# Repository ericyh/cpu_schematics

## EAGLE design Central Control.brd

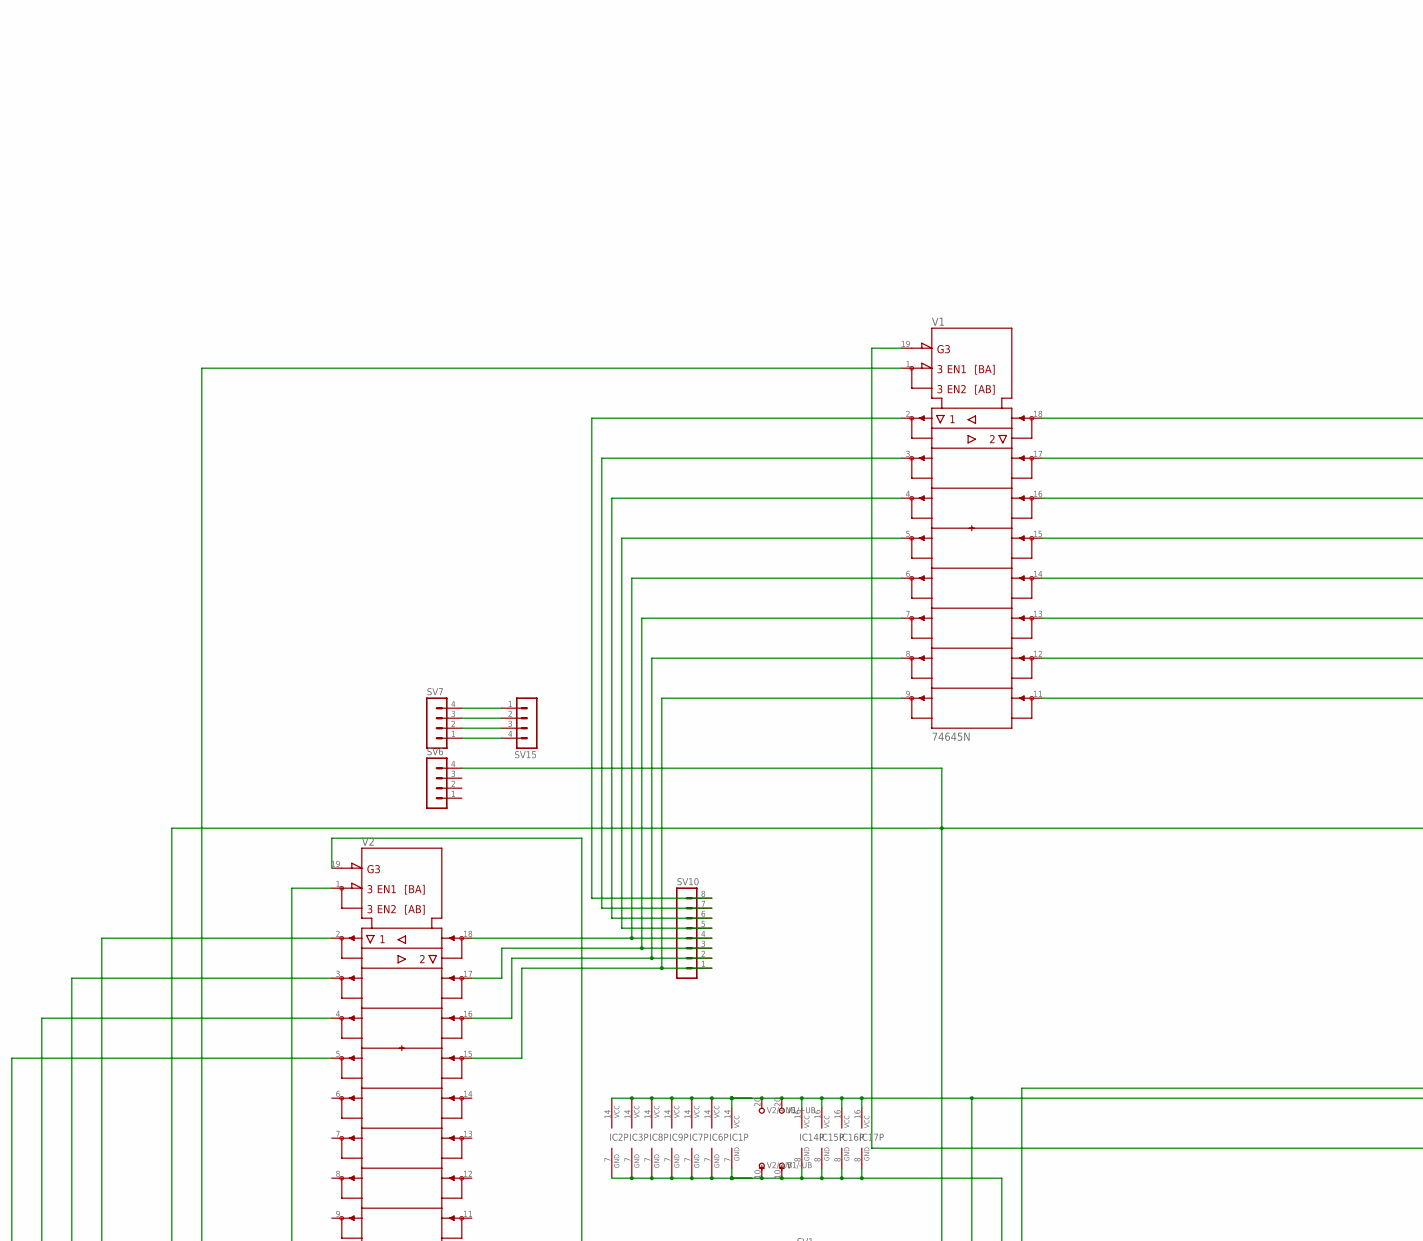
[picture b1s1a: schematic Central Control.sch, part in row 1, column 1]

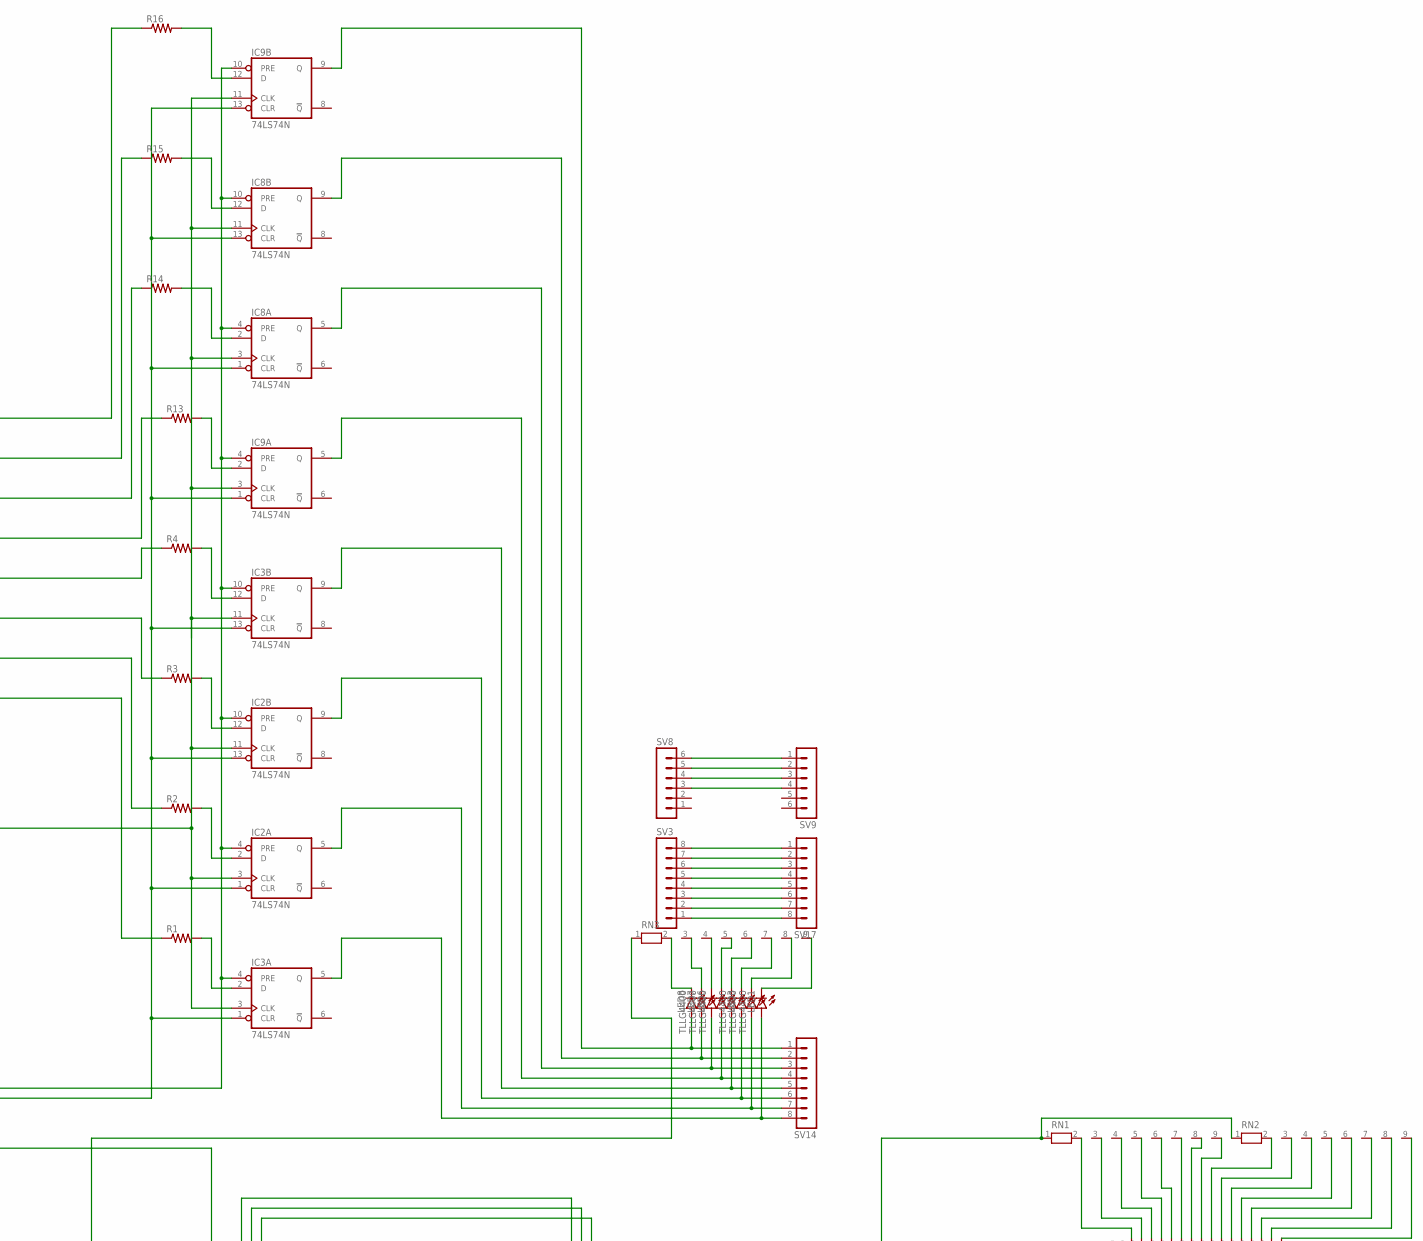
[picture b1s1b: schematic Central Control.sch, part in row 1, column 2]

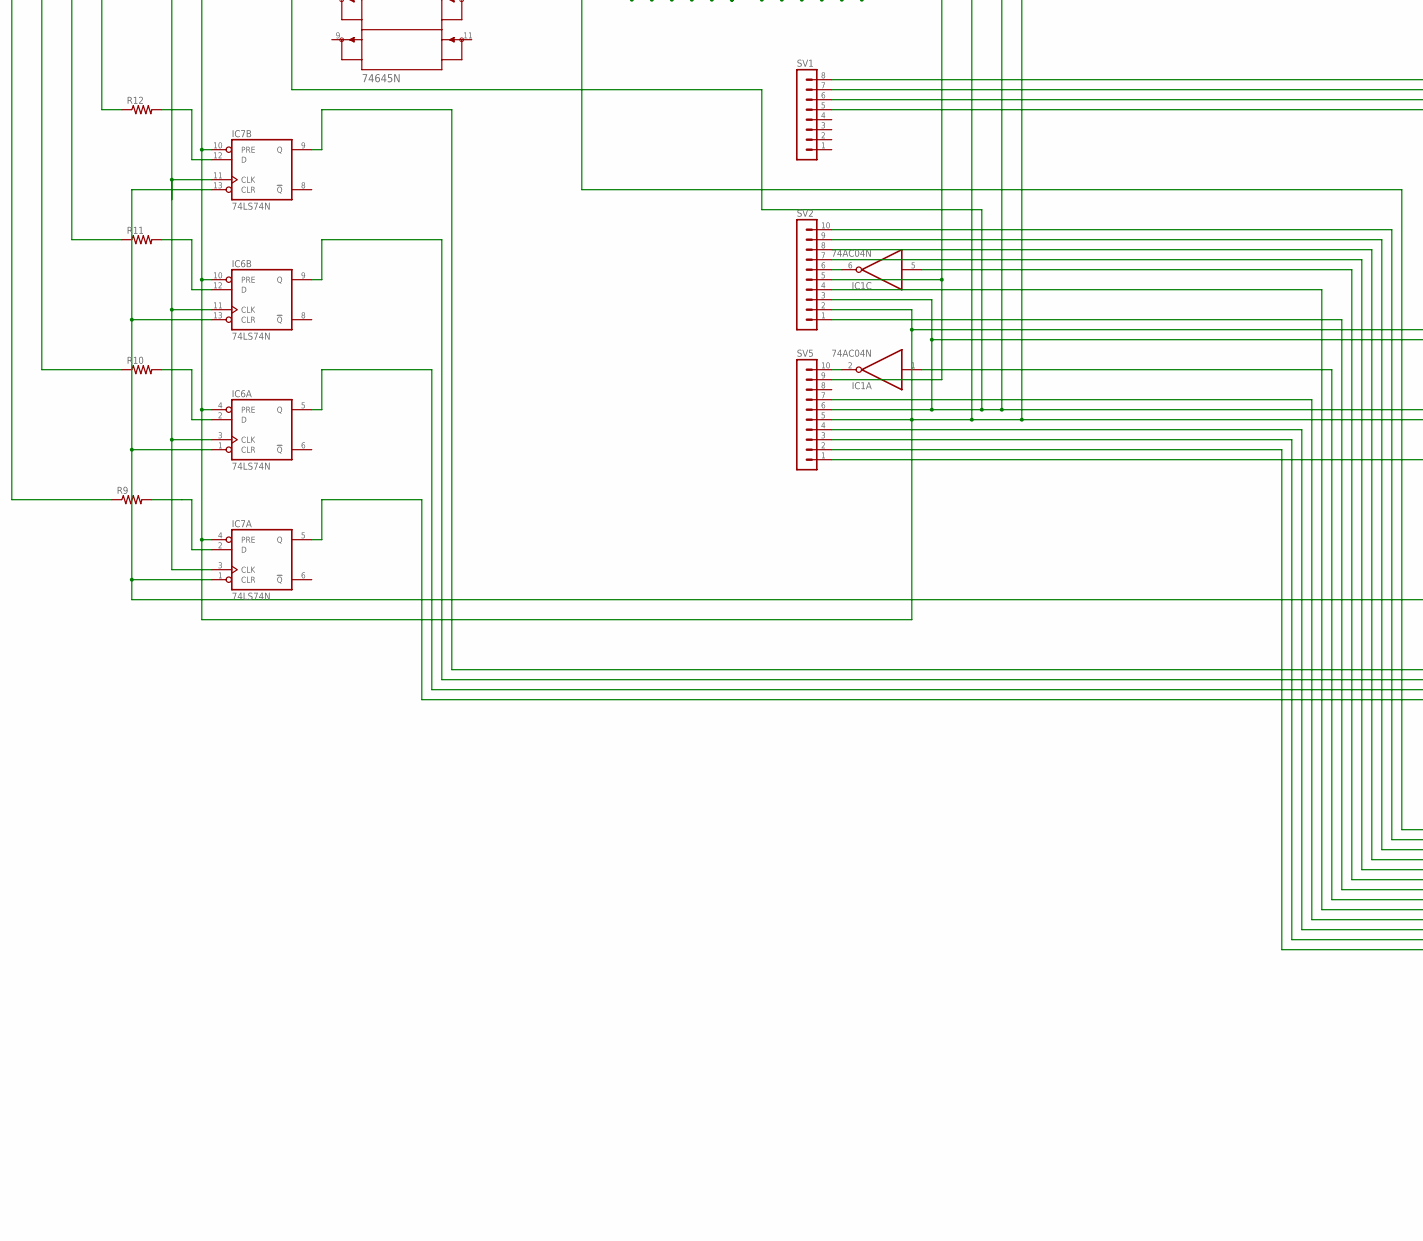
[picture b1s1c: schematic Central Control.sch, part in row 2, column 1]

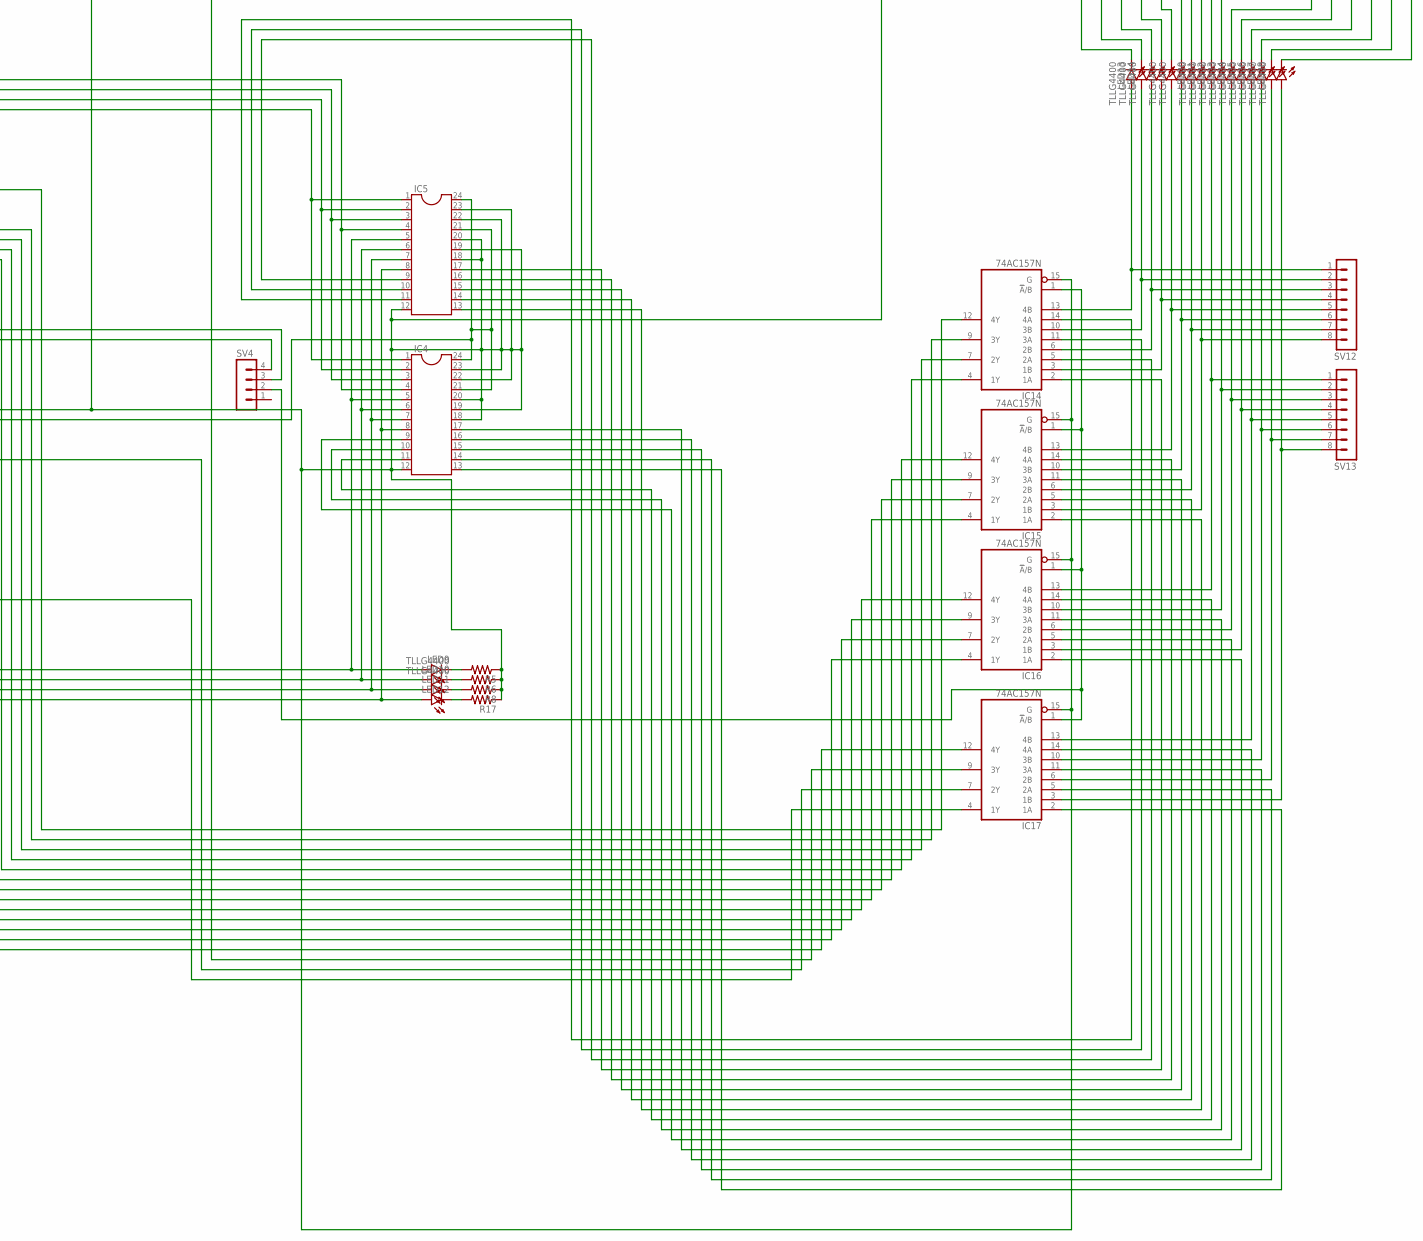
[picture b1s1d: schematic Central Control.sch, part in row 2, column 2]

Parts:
IC1: 74AC04N; DIL14
IC2, IC3, IC6, IC7, IC8, IC9: 74LS74N; DIL14
IC4, IC5: DIL24-6
IC14, IC15, IC16, IC17: 74AC157N; DIL16
LED1, LED2, LED3, LED4, LED5, LED6, LED7, LED8, LED9, LED10, LED11, LED12, LED13, LED14, LED15, LED16, LED18, LED19, LED20, LED21, LED22, LED23, LED24, LED25, LED26, LED27, LED28, LED29: TLLG4400; LED3MM
R1, R2, R3, R4, R5, R6, R8, R9, R10, R11, R12, R13, R14, R15, R16, R17: R-US_0207/2V; 0207/2V
RN1, RN2, RN3: RN08; RN-9
SV1, SV3, SV10, SV12, SV13, SV14, SV17: MA08-1
SV2, SV5: MA10-1
SV4, SV6, SV7, SV15: MA04-1
SV8, SV9: MA06-1
V1, V2: 74645N; DIL20

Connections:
unnamed: IC1.5 (I), IC15.9 (3Y)
unnamed: IC4.8, IC5.8, IC7.5 (Q), LED12.A
unnamed: IC14.13 (4B), LED13.A, SV12.1
unnamed: IC4.14, IC17.5 (2A)
unnamed: IC17.3 (1B), LED29.A, SV13.8
unnamed: SV10.5, V1.5 (A4)
unnamed: SV10.6, V1.4 (A3)
unnamed: SV10.7, V1.3 (A2)
unnamed: SV10.8, V1.2 (A1)
unnamed: SV10.4, V1.6 (A5), V2.18 (B1)
unnamed: IC4.1, IC5.1, SV1.5
unnamed: SV10.3, V1.7 (A6), V2.17 (B2)
unnamed: R10.1, V2.4 (A3)
unnamed: R9.1, V2.5 (A4)
unnamed: IC1.1 (I), IC15.4 (1Y)
unnamed: IC3.9 (Q), LED4.A, SV14.5
unnamed: IC17.6 (2B), LED28.A, SV13.7
unnamed: IC17.10 (3B), LED27.A, SV13.6
unnamed: IC4.16, IC17.14 (4A)
unnamed: IC1.7 (GND), IC2.7 (GND), IC3.7 (GND), IC4.12, IC4.18, IC4.19, IC4.20, IC4.22, IC4.23, IC5.12, IC5.18, IC5.19, IC5.20, IC5.22, IC5.23, IC6.7 (GND), IC7.7 (GND), IC8.7 (GND), IC9.7 (GND), IC14.8 (GND), IC14.15 (G), IC15.8 (GND), IC15.15 (G), IC16.8 (GND), IC16.15 (G), IC17.8 (GND), IC17.15 (G), R5.1, R6.1, R8.1, R17.1, RN1.1, RN2.1, RN3.1, SV2.3, SV4.4, SV5.6, V1.10 (-UB), V2.1 (DIR), V2.10 (-UB)
unnamed: IC5.10, IC14.11 (3A)
unnamed: IC5.11, IC14.14 (4A)
unnamed: IC16.13 (4B), LED22.A, SV13.1
unnamed: IC16.10 (3B), LED23.A, SV13.2
unnamed: IC16.6 (2B), LED24.A, SV13.3
unnamed: IC16.3 (1B), LED25.A, SV13.4
unnamed: IC17.13 (4B), LED26.A, SV13.5
unnamed: IC4.13, IC17.2 (1A)
unnamed: IC2.3 (CLK), IC2.11 (CLK), IC3.3 (CLK), IC3.11 (CLK), IC6.3 (CLK), IC6.11 (CLK), IC7.3 (CLK), IC7.11 (CLK), IC8.3 (CLK), IC8.11 (CLK), IC9.3 (CLK), IC9.11 (CLK), SV2.5, SV5.9, SV6.4
unnamed: IC4.5, IC5.5, IC7.9 (Q), LED9.A
unnamed: R3.1, V1.13 (B6)
unnamed: R4.1, V1.14 (B5)
unnamed: IC4.6, IC5.6, IC6.9 (Q), LED10.A
unnamed: IC4.7, IC5.7, IC6.5 (Q), LED11.A
unnamed: R1.1, V1.11 (B8)
unnamed: IC2.9 (Q), LED3.A, SV14.6
unnamed: IC2.5 (Q), LED2.A, SV14.7
unnamed: IC3.5 (Q), LED1.A, SV14.8
unnamed: IC4.2, IC5.2, SV1.6
unnamed: IC4.4, IC5.4, SV1.8
unnamed: R14.1, V1.16 (B3)
unnamed: IC4.3, IC5.3, SV1.7
unnamed: IC17.9 (3Y), V1.19 (!G)
unnamed: IC6.1 (CLR), IC6.13 (CLR), IC7.1 (CLR), IC7.13 (CLR), IC17.4 (1Y)
unnamed: SV7.4, SV15.1
unnamed: R13.1, V1.15 (B4)
unnamed: IC9.9 (Q), LED8.A, SV14.1
unnamed: IC8.9 (Q), LED7.A, SV14.2
unnamed: IC9.5 (Q), LED5.A, SV14.4
unnamed: R15.1, V1.17 (B2)
unnamed: IC8.5 (Q), LED6.A, SV14.3
unnamed: SV7.3, SV15.2
unnamed: IC14.10 (3B), LED14.A, SV12.2
unnamed: R16.1, V1.18 (B1)
unnamed: R2.1, V1.12 (B7)
unnamed: IC1.14 (VCC), IC2.1 (CLR), IC2.4 (PRE), IC2.10 (PRE), IC2.13 (CLR), IC2.14 (VCC), IC3.1 (CLR), IC3.4 (PRE), IC3.10 (PRE), IC3.13 (CLR), IC3.14 (VCC), IC4.21, IC4.24, IC5.21, IC5.24, IC6.4 (PRE), IC6.10 (PRE), IC6.14 (VCC), IC7.4 (PRE), IC7.10 (PRE), IC7.14 (VCC), IC8.1 (CLR), IC8.4 (PRE), IC8.10 (PRE), IC8.13 (CLR), IC8.14 (VCC), IC9.1 (CLR), IC9.4 (PRE), IC9.10 (PRE), IC9.13 (CLR), IC9.14 (VCC), IC14.16 (VCC), IC15.16 (VCC), IC16.16 (VCC), IC17.16 (VCC), SV2.2, SV4.3, SV5.5, V1.1 (DIR), V1.20 (+UB), V2.20 (+UB)
unnamed: SV7.2, SV15.3
unnamed: SV7.1, SV15.4
unnamed: SV8.6, SV9.1
unnamed: SV8.5, SV9.2
unnamed: SV8.4, SV9.3
unnamed: SV8.3, SV9.4
unnamed: SV3.8, SV17.1
unnamed: SV3.7, SV17.2
unnamed: SV3.6, SV17.3
unnamed: SV3.5, SV17.4
unnamed: SV3.4, SV17.5
unnamed: SV3.3, SV17.6
unnamed: SV3.2, SV17.7
unnamed: SV3.1, SV17.8
unnamed: R12.1, V2.2 (A1)
unnamed: SV10.2, V1.8 (A7), V2.16 (B3)
unnamed: R11.1, V2.3 (A2)
unnamed: SV10.1, V1.9 (A8), V2.15 (B4)
unnamed: IC14.7 (2Y), SV2.9
unnamed: IC1.6 (O), SV2.6
unnamed: IC14.3 (1B), LED16.A, SV12.4
unnamed: IC14.6 (2B), LED15.A, SV12.3
unnamed: IC15.13 (4B), LED18.A, SV12.5
unnamed: LED7.K (C), RN3.3
unnamed: IC7.12 (D), R12.2
unnamed: LED11.K (C), R8.2
unnamed: IC6.12 (D), R11.2
unnamed: IC15.3 (1B), LED21.A, SV12.8
unnamed: IC15.6 (2B), LED20.A, SV12.7
unnamed: IC15.10 (3B), LED19.A, SV12.6
unnamed: IC5.17, IC14.2 (1A)
unnamed: IC5.9, IC14.5 (2A)
unnamed: IC5.16, IC15.14 (4A)
unnamed: IC5.15, IC15.11 (3A)
unnamed: IC5.14, IC15.5 (2A)
unnamed: IC5.13, IC15.2 (1A)
unnamed: IC4.17, IC16.2 (1A)
unnamed: IC14.12 (4Y), V2.19 (!G)
unnamed: IC14.1 (!A!/B), IC15.1 (!A!/B), IC16.1 (!A!/B), IC17.1 (!A!/B), SV4.2
unnamed: IC1.2 (O), SV5.10
unnamed: IC4.10, IC16.11 (3A)
unnamed: IC14.4 (1Y), SV2.8
unnamed: IC15.12 (4Y), SV2.7
unnamed: IC4.15, IC17.11 (3A)
unnamed: IC15.7 (2Y), SV2.1
unnamed: IC4.9, IC16.5 (2A)
unnamed: IC16.12 (4Y), SV2.4
unnamed: IC16.7 (2Y), SV5.4
unnamed: IC16.9 (3Y), SV5.7
unnamed: IC4.11, IC16.14 (4A)
unnamed: IC17.12 (4Y), SV5.2
unnamed: IC17.7 (2Y), SV5.1
unnamed: IC6.2 (D), R10.2
unnamed: IC7.2 (D), R9.2
unnamed: IC9.12 (D), R16.2
unnamed: IC16.4 (1Y), SV5.3
unnamed: IC14.9 (3Y), SV2.10
unnamed: IC8.12 (D), R15.2
unnamed: IC8.2 (D), R14.2
unnamed: IC9.2 (D), R13.2
unnamed: IC3.12 (D), R4.2
unnamed: IC2.12 (D), R3.2
unnamed: IC2.2 (D), R2.2
unnamed: IC3.2 (D), R1.2
unnamed: LED13.K (C), RN1.2
unnamed: LED14.K (C), RN1.3
unnamed: LED15.K (C), RN1.4
unnamed: LED16.K (C), RN1.5
unnamed: LED18.K (C), RN1.6
unnamed: LED19.K (C), RN1.7
unnamed: LED20.K (C), RN1.8
unnamed: LED21.K (C), RN1.9
unnamed: LED22.K (C), RN2.2
unnamed: LED23.K (C), RN2.3
unnamed: LED24.K (C), RN2.4
unnamed: LED25.K (C), RN2.5
unnamed: LED26.K (C), RN2.6
unnamed: LED27.K (C), RN2.7
unnamed: LED28.K (C), RN2.8
unnamed: LED29.K (C), RN2.9
unnamed: LED8.K (C), RN3.2
unnamed: LED6.K (C), RN3.4
unnamed: LED5.K (C), RN3.5
unnamed: LED4.K (C), RN3.6
unnamed: LED3.K (C), RN3.7
unnamed: LED2.K (C), RN3.8
unnamed: LED1.K (C), RN3.9
unnamed: LED9.K (C), R5.2
unnamed: LED10.K (C), R6.2
unnamed: LED12.K (C), R17.2

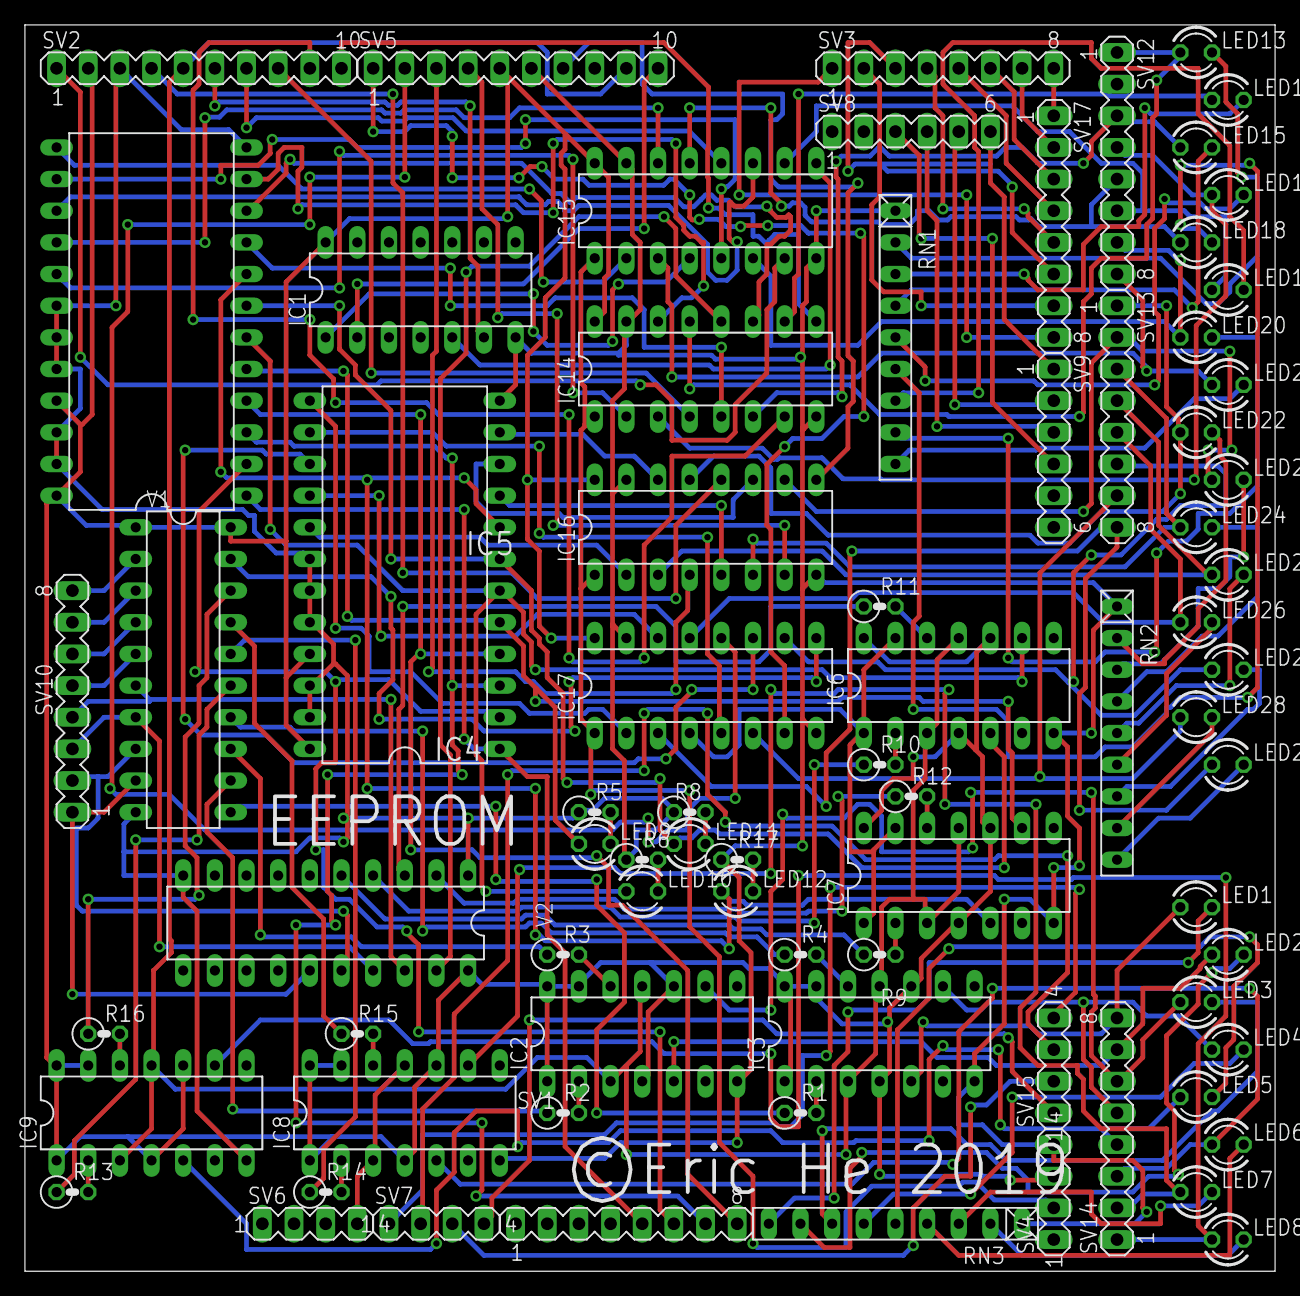
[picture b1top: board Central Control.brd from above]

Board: 2 copper layers, 100.3 x 100.0 mm, 77 parts (0 on the bottom side), 146 nets.

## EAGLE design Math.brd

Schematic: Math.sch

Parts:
IC1, IC2, IC3, IC4, IC5, IC6, IC7, IC8: 74LS74N; DIL14
IC9, IC10: 74LS83N; DIL16
IC11, IC12: 74AC86N; DIL14
LED1, LED2, LED3, LED4, LED5, LED6, LED7, LED8, LED9, LED10, LED11, LED12, LED13, LED14, LED15, LED16, LED17, LED18, LED19, LED20, LED21, LED22, LED23, LED24: TLLY4400; LED3MM
R1, R2, R3, R4, R5, R6, R7, R8, R9, R10, R11, R12, R13, R14, R15, R16: R-US_0207/2V; 0207/2V
RN1, RN2, RN3: RN08; RN-9
SV1, SV8: MA10-1
SV2, SV6, SV7: MA08-1
SV3: MA06-1
SV4, SV5: MA04-1
V1, V2, V3, V4: 74645N; DIL20

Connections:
unnamed: IC9.14 (C4), IC10.13 (C0)
unnamed: SV1.3, V2.19 (!G)
unnamed: R7.1, V2.14 (B5)
unnamed: SV1.2, V4.19 (!G)
unnamed: R1.1, V2.11 (B8)
unnamed: IC1.1 (CLR), IC1.13 (CLR), IC2.1 (CLR), IC2.13 (CLR), IC3.1 (CLR), IC3.13 (CLR), IC4.1 (CLR), IC4.13 (CLR), SV1.10
unnamed: IC1.9 (Q), IC12.4 (I0), LED6.A, V4.13 (B6)
unnamed: IC1.5 (Q), IC12.12 (I0), LED7.A, V4.12 (B7)
unnamed: IC9.4 (B3), IC11.8 (O)
unnamed: IC9.13 (C0), IC11.2 (I1), IC11.5 (I1), IC11.10 (I1), IC11.13 (I1), IC12.2 (I1), IC12.5 (I1), IC12.10 (I1), IC12.13 (I1), SV1.7
unnamed: IC2.9 (Q), IC12.1 (I0), LED5.A, V4.14 (B5)
unnamed: R5.1, V2.16 (B3)
unnamed: IC3.5 (Q), IC11.9 (I0), LED3.A, V4.16 (B3)
unnamed: R6.1, V2.15 (B4)
unnamed: IC4.9 (Q), IC11.1 (I0), LED1.A
unnamed: IC3.9 (Q), IC11.4 (I0), LED2.A, V4.17 (B2)
unnamed: IC9.7 (B2), IC11.6 (O)
unnamed: IC4.5 (Q), IC11.12 (I0), LED4.A, V4.15 (B4)
unnamed: IC1.3 (CLK), IC1.11 (CLK), IC2.3 (CLK), IC2.11 (CLK), IC3.3 (CLK), IC3.11 (CLK), IC4.3 (CLK), IC4.11 (CLK), IC5.3 (CLK), IC5.11 (CLK), IC6.3 (CLK), IC6.11 (CLK), IC7.3 (CLK), IC7.11 (CLK), IC8.3 (CLK), IC8.11 (CLK), SV1.9
unnamed: IC2.5 (Q), IC12.9 (I0), LED8.A, V4.11 (B8)
unnamed: R4.1, V2.17 (B2)
unnamed: R11.1, V1.13 (B6)
unnamed: R2.1, V2.12 (B7)
unnamed: R12.1, V1.14 (B5)
unnamed: R9.1, V1.11 (B8)
unnamed: IC5.9 (Q), IC10.8 (A2), LED14.A
unnamed: IC5.5 (Q), IC10.3 (A3), LED15.A
unnamed: IC6.5 (Q), IC10.1 (A4), LED16.A
unnamed: R14.1, V1.16 (B3)
unnamed: SV1.4, V1.19 (!G)
unnamed: R13.1, V1.15 (B4)
unnamed: IC8.9 (Q), IC9.10 (A1), LED9.A
unnamed: IC7.9 (Q), IC9.8 (A2), LED10.A
unnamed: IC8.5 (Q), IC9.1 (A4), LED12.A
unnamed: R15.1, V1.17 (B2)
unnamed: IC7.5 (Q), IC9.3 (A3), LED11.A
unnamed: IC6.9 (Q), IC10.10 (A1), LED13.A
unnamed: IC5.1 (CLR), IC5.13 (CLR), IC6.1 (CLR), IC6.13 (CLR), IC7.1 (CLR), IC7.13 (CLR), IC8.1 (CLR), IC8.13 (CLR), SV1.8
unnamed: LED16.K (C), RN2.9
unnamed: IC1.4 (PRE), IC1.10 (PRE), IC1.14 (VCC), IC2.4 (PRE), IC2.10 (PRE), IC2.14 (VCC), IC3.4 (PRE), IC3.10 (PRE), IC3.14 (VCC), IC4.4 (PRE), IC4.10 (PRE), IC4.14 (VCC), IC5.4 (PRE), IC5.10 (PRE), IC5.14 (VCC), IC6.4 (PRE), IC6.10 (PRE), IC6.14 (VCC), IC7.4 (PRE), IC7.10 (PRE), IC7.14 (VCC), IC8.4 (PRE), IC8.10 (PRE), IC8.14 (VCC), IC9.5 (VCC), IC10.5 (VCC), IC11.14 (VCC), IC12.14 (VCC), SV1.5, V1.1 (DIR), V1.20 (+UB), V2.1 (DIR), V2.20 (+UB), V3.1 (DIR), V3.20 (+UB), V4.20 (+UB)
unnamed: IC9.11 (B1), IC11.3 (O)
unnamed: IC1.7 (GND), IC2.7 (GND), IC3.7 (GND), IC4.7 (GND), IC5.7 (GND), IC6.7 (GND), IC7.7 (GND), IC8.7 (GND), IC9.12 (GND), IC10.12 (GND), IC11.7 (GND), IC12.7 (GND), RN1.1, RN2.1, RN3.1, SV1.6, V1.10 (-UB), V2.10 (-UB), V3.10 (-UB), V4.1 (DIR), V4.10 (-UB)
unnamed: IC9.16 (B4), IC11.11 (O)
unnamed: IC10.11 (B1), IC12.3 (O)
unnamed: IC10.4 (B3), IC12.11 (O)
unnamed: IC10.7 (B2), IC12.6 (O)
unnamed: IC10.16 (B4), IC12.8 (O)
unnamed: R16.1, V1.18 (B1)
unnamed: R10.1, V1.12 (B7)
unnamed: SV1.1, V3.19 (!G)
unnamed: R3.1, V2.13 (B6)
unnamed: IC10.2 (S3), LED23.A, V3.8 (A7)
unnamed: R8.1, V2.18 (B1)
unnamed: LED15.K (C), RN2.8
unnamed: IC9.15 (S4), LED20.A, V3.5 (A4)
unnamed: LED1.K (C), RN1.9
unnamed: IC6.2 (D), R9.2
unnamed: IC5.2 (D), R10.2
unnamed: IC5.12 (D), R11.2
unnamed: SV2.8, V1.2 (A1), V2.2 (A1), V3.18 (B1), V4.2 (A1)
unnamed: SV2.7, V1.3 (A2), V2.3 (A2), V3.17 (B2), V4.3 (A2)
unnamed: IC6.12 (D), R12.2
unnamed: SV2.6, V1.4 (A3), V2.4 (A3), V3.16 (B3), V4.4 (A3)
unnamed: SV2.5, V1.5 (A4), V2.5 (A4), V3.15 (B4), V4.5 (A4)
unnamed: SV2.3, V1.7 (A6), V2.7 (A6), V3.13 (B6), V4.7 (A6)
unnamed: SV2.4, V1.6 (A5), V2.6 (A5), V3.14 (B5), V4.6 (A5)
unnamed: SV2.1, V1.9 (A8), V2.9 (A8), V3.11 (B8), V4.9 (A8)
unnamed: SV2.2, V1.8 (A7), V2.8 (A7), V3.12 (B7), V4.8 (A7)
unnamed: IC8.2 (D), R13.2
unnamed: IC7.2 (D), R14.2
unnamed: IC9.2 (S3), LED19.A, V3.4 (A3)
unnamed: IC9.6 (S2), LED18.A, V3.3 (A2)
unnamed: IC9.9 (S1), LED17.A, V3.2 (A1)
unnamed: IC10.9 (S1), LED21.A, V3.6 (A5)
unnamed: IC10.6 (S2), LED22.A, V3.7 (A6)
unnamed: IC10.15 (S4), LED24.A, V3.9 (A8)
unnamed: IC7.12 (D), R15.2
unnamed: IC8.12 (D), R16.2
unnamed: IC4.12 (D), R8.2
unnamed: IC3.12 (D), R4.2
unnamed: IC3.2 (D), R5.2
unnamed: IC4.2 (D), R6.2
unnamed: IC2.12 (D), R7.2
unnamed: IC1.12 (D), R3.2
unnamed: IC1.2 (D), R2.2
unnamed: IC2.2 (D), R1.2
unnamed: LED2.K (C), RN1.8
unnamed: LED4.K (C), RN1.6
unnamed: LED3.K (C), RN1.7
unnamed: LED6.K (C), RN1.4
unnamed: LED5.K (C), RN1.5
unnamed: LED7.K (C), RN1.3
unnamed: LED8.K (C), RN1.2
unnamed: LED14.K (C), RN2.7
unnamed: LED13.K (C), RN2.6
unnamed: LED12.K (C), RN2.5
unnamed: LED11.K (C), RN2.4
unnamed: LED10.K (C), RN2.3
unnamed: LED9.K (C), RN2.2
unnamed: LED24.K (C), RN3.9
unnamed: LED23.K (C), RN3.8
unnamed: LED22.K (C), RN3.7
unnamed: LED21.K (C), RN3.6
unnamed: LED20.K (C), RN3.5
unnamed: LED19.K (C), RN3.4
unnamed: LED18.K (C), RN3.3
unnamed: LED17.K (C), RN3.2

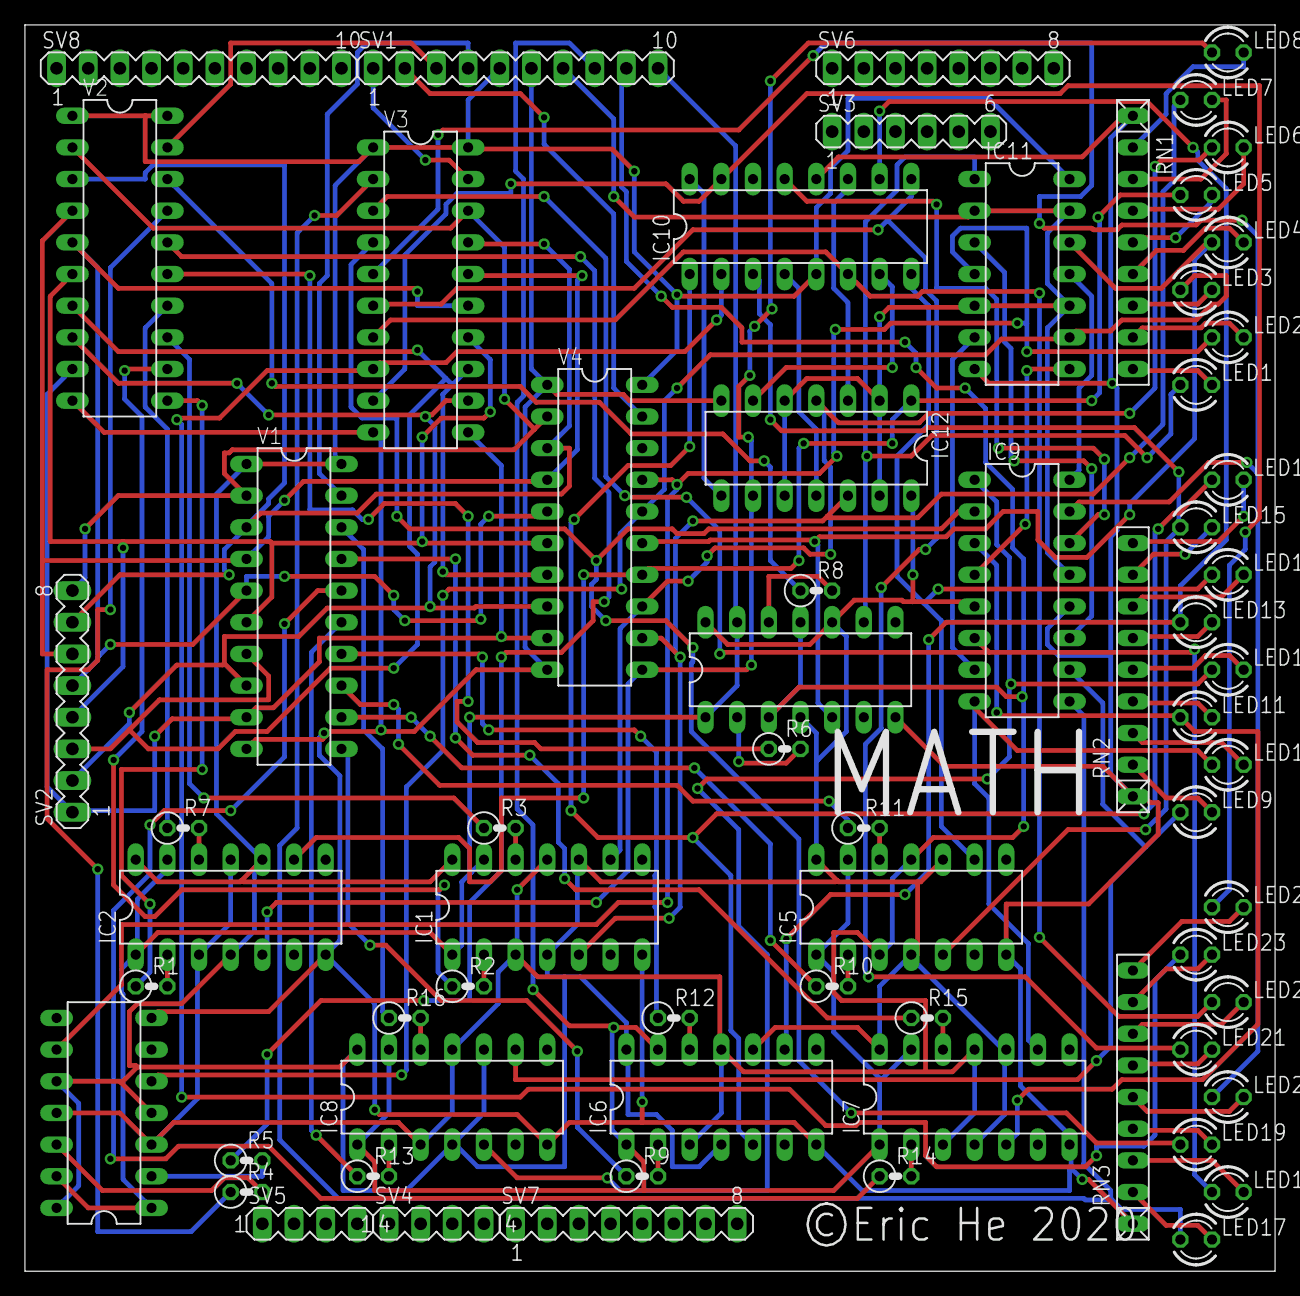
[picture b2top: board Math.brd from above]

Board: 2 copper layers, 100.3 x 100.0 mm, 67 parts (0 on the bottom side), 107 nets.

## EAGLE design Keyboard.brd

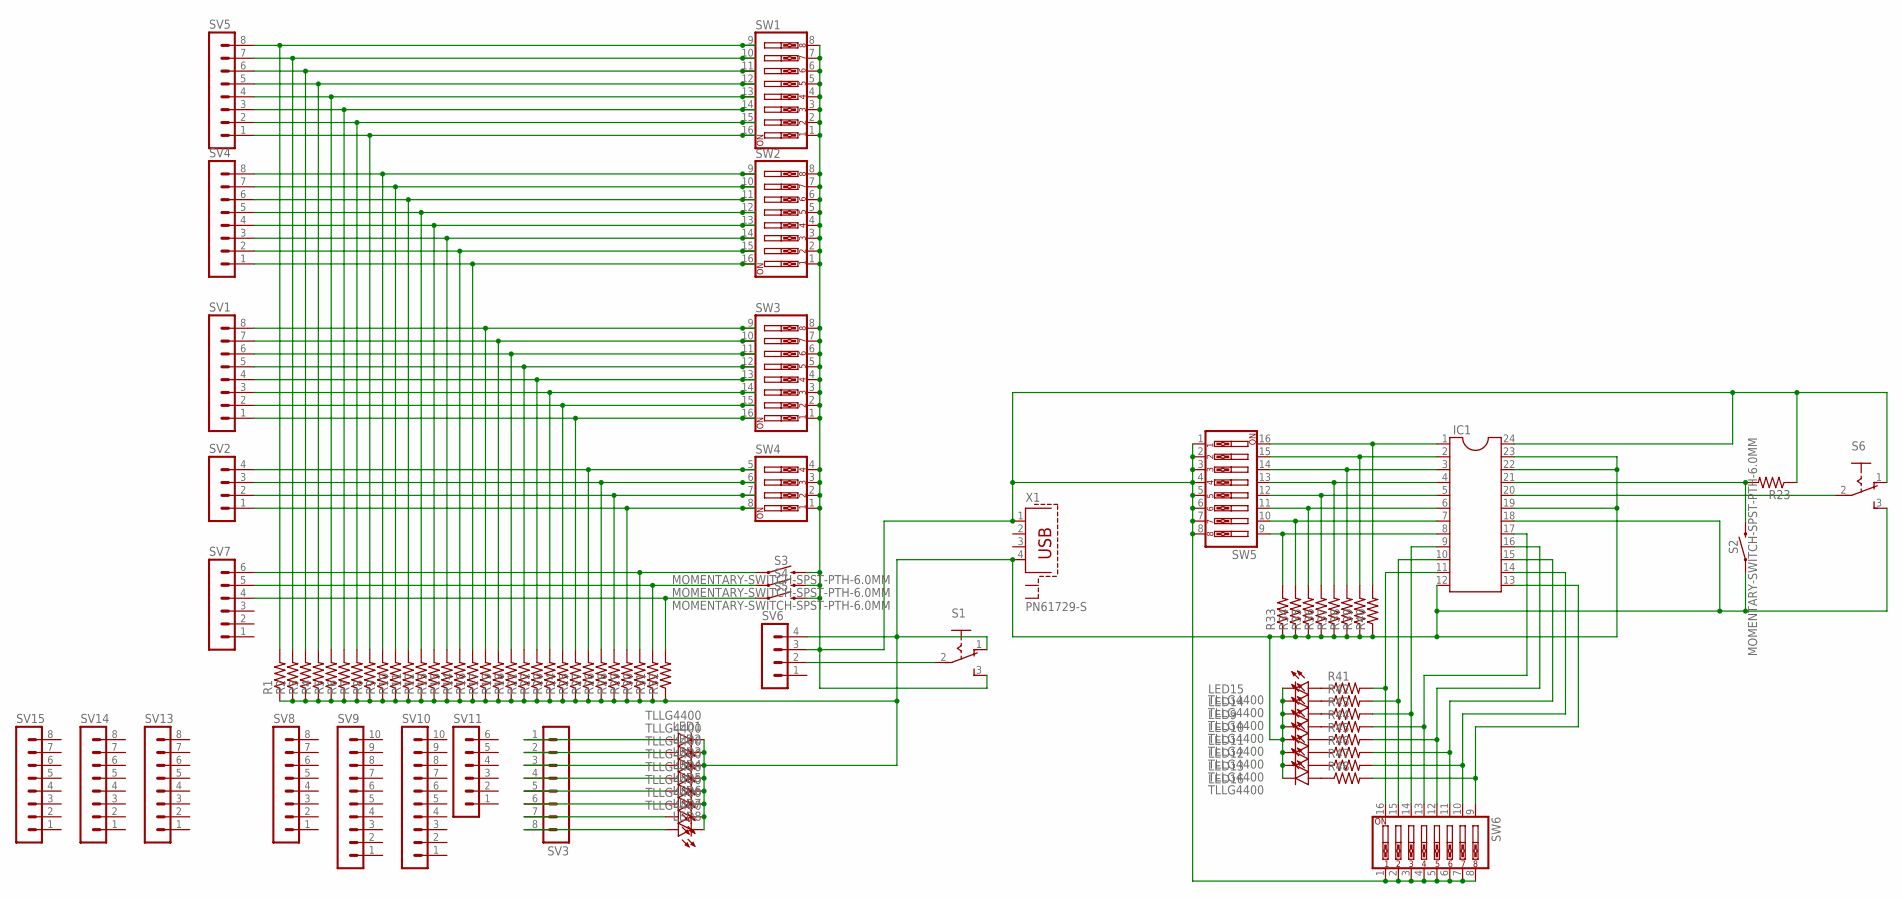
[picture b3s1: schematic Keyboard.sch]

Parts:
IC1: DIL24-6
LED1, LED2, LED3, LED4, LED5, LED6, LED7, LED8, LED9, LED10, LED11, LED12, LED13, LED14, LED15, LED16: TLLG4400; LED3MM
R1, R2, R3, R4, R5, R6, R7, R8, R9, R10, R11, R12, R13, R14, R15, R16, R17, R18, R19, R20, R21, R22, R23, R24, R25, R26, R27, R28, R29, R30, R31, R32, R33, R34, R35, R36, R37, R38, R39, R40, R41, R42, R43, R44, R45, R46, R47, R48: R-US_0207/2V; 0207/2V
S1, S6: M251
S2, S3, S4, S5: MOMENTARY-SWITCH-SPST-PTH-6.0MM; TACTILE_SWITCH_PTH_6.0MM
SV1, SV3, SV4, SV5, SV8, SV13, SV14, SV15: MA08-1
SV2, SV6: MA04-1
SV7, SV11: MA06-1
SV9, SV10: MA10-1
SW1, SW2, SW3, SW5, SW6: SW_DIP-8; EDG-08
SW4: SW_DIP-4; EDG-04
X1: PN61729-S

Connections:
unnamed: R17.2, SV1.8, SW3.9
unnamed: R19.2, SV1.7, SW3.10
unnamed: R18.2, SV1.6, SW3.11
unnamed: R21.2, SV1.5, SW3.12
unnamed: R22.2, SV1.4, SW3.13
unnamed: R20.2, SV1.3, SW3.14
unnamed: R24.2, SV1.2, SW3.15
unnamed: R25.2, SV1.1, SW3.16
unnamed: R27.2, SV2.4, SW4.5
unnamed: R26.2, SV2.3, SW4.6
unnamed: R28.2, SV2.2, SW4.7
unnamed: R29.2, SV2.1, SW4.8
unnamed: R30.2, S3.1, SV7.6
unnamed: R31.2, S4.1, SV7.5
unnamed: R32.2, S5.1, SV7.4
unnamed: R9.2, SV4.8, SW2.9
unnamed: R10.2, SV4.7, SW2.10
unnamed: R11.2, SV4.6, SW2.11
unnamed: R12.2, SV4.5, SW2.12
unnamed: R13.2, SV4.4, SW2.13
unnamed: R15.2, SV4.3, SW2.14
unnamed: R14.2, SV4.2, SW2.15
unnamed: R16.2, SV4.1, SW2.16
unnamed: R1.2, SV5.8, SW1.9
unnamed: R2.2, SV5.7, SW1.10
unnamed: R3.2, SV5.6, SW1.11
unnamed: R4.2, SV5.5, SW1.12
unnamed: R5.2, SV5.4, SW1.13
unnamed: R6.2, SV5.3, SW1.14
unnamed: R7.2, SV5.2, SW1.15
unnamed: R8.2, SV5.1, SW1.16
unnamed: IC1.9, R43.2, SW6.14
unnamed: IC1.24, R23.1, S1.3 (S), S3.3 (2), S4.3 (2), S5.3 (2), S6.1 (O), SV6.3, SW1.1, SW1.2, SW1.3, SW1.4, SW1.5, SW1.6, SW1.7, SW1.8, SW2.1, SW2.2, SW2.3, SW2.4, SW2.5, SW2.6, SW2.7, SW2.8, SW3.1, SW3.2, SW3.3, SW3.4, SW3.5, SW3.6, SW3.7, SW3.8, SW4.1, SW4.2, SW4.3, SW4.4, SW5.1, SW5.2, SW5.3, SW5.4, SW5.5, SW5.6, SW5.7, SW5.8, SW6.1, SW6.2, SW6.3, SW6.4, SW6.5, SW6.6, SW6.7, SW6.8, X1.1
unnamed: IC1.20, S6.2
unnamed: LED1.A, SV3.1
unnamed: LED2.A, SV3.2
unnamed: LED3.A, SV3.3
unnamed: LED4.A, SV3.4
unnamed: LED5.A, SV3.5
unnamed: LED6.A, SV3.6
unnamed: LED7.A, SV3.7
unnamed: LED8.A, SV3.8
unnamed: IC1.12, IC1.18, IC1.19, IC1.22, IC1.23, LED1.K (C), LED2.K (C), LED3.K (C), LED4.K (C), LED5.K (C), LED6.K (C), LED7.K (C), LED8.K (C), LED9.K (C), LED10.K (C), LED11.K (C), LED12.K (C), LED13.K (C), LED14.K (C), LED15.K (C), LED16.K (C), R1.1, R2.1, R3.1, R4.1, R5.1, R6.1, R7.1, R8.1, R9.1, R10.1, R11.1, R12.1, R13.1, R14.1, R15.1, R16.1, R17.1, R18.1, R19.1, R20.1, R21.1, R22.1, R24.1, R25.1, R26.1, R27.1, R28.1, R29.1, R30.1, R31.1, R32.1, R33.1, R34.1, R35.1, R36.1, R37.1, R38.1, R39.1, R40.1, S1.1 (O), S2.1, S6.3 (S), SV6.4, X1.4
unnamed: IC1.10, R42.2, SW6.15
unnamed: IC1.21, R23.2, S2.3 (2)
unnamed: IC1.11, R41.2, SW6.16
unnamed: IC1.17, R44.2, SW6.13
unnamed: IC1.16, R45.2, SW6.12
unnamed: IC1.15, R46.2, SW6.11
unnamed: IC1.14, R47.2, SW6.10
unnamed: IC1.13, R48.2, SW6.9
unnamed: IC1.1, R40.2, SW5.16
unnamed: IC1.2, R39.2, SW5.15
unnamed: IC1.3, R38.2, SW5.14
unnamed: IC1.4, R37.2, SW5.13
unnamed: IC1.5, R36.2, SW5.12
unnamed: IC1.6, R35.2, SW5.11
unnamed: IC1.7, R34.2, SW5.10
unnamed: IC1.8, R33.2, SW5.9
unnamed: LED15.A, R41.1
unnamed: LED14.A, R42.1
unnamed: LED9.A, R43.1
unnamed: LED10.A, R44.1
unnamed: LED11.A, R45.1
unnamed: LED12.A, R46.1
unnamed: LED13.A, R47.1
unnamed: LED16.A, R48.1
unnamed: S1.2, SV6.2

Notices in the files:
Central Control.brd:
©Eric He 2019
Keyboard.brd:
8-Bit CPU ©Eric He
Math.brd:
©Eric He 2020
parts and their libraries:
SparkFun-Switches: Licensing: Creative Commons ShareAlike 4.0 International - https://creativecommons.org/licenses/by-sa/4.0
